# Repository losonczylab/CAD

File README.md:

# Hardware
Includes AutoDesk Inventor projects used for lab rigs, other miscellaneous CAD files, Adobe Illustrator files used for laser cutting, and user guides for constructing assemblies.

## Useful Programs
  - <a href="https://www.arduino.cc/en/software">Arduino IDE</a> - used to flash the Behavior Controller and Position Controller programs onto the Arduino Due and Arduino Nanos respectively.
  - <a href="https://www.kicad.org/">KiCad</a>
  - <a href ="https://www.autodesk.com/products/inventor">AutoDesk Inventor 2024 or Later (academic licenses available)</a>

## Electronics
  - Arduino program for Behavior Controller and Position Controller
  - KiCad files for PCB boards for the Behavior and Position Controllers
  - PDF manual for assembling a complete electronics box

## Full-Size-Rig
  - CAD files for frames holding full size displays

## Illustrator Files
- Adobe Illustrator files for custom made parts from laser-cut arylic

## Implant
- CAD files for metal implant used to head-fix mice.

## Implant Holder
- CAD files for implant holder.

## Tablet Rig
  - CAD files for frames holding tablet displays

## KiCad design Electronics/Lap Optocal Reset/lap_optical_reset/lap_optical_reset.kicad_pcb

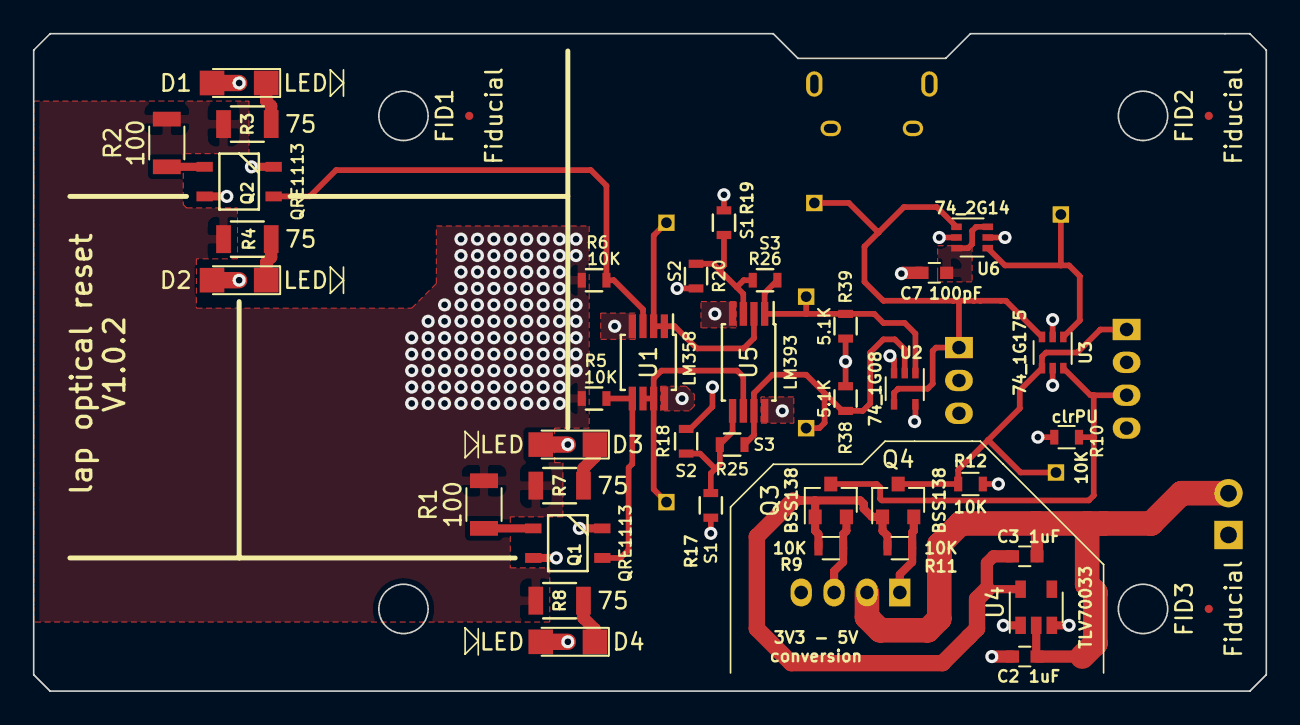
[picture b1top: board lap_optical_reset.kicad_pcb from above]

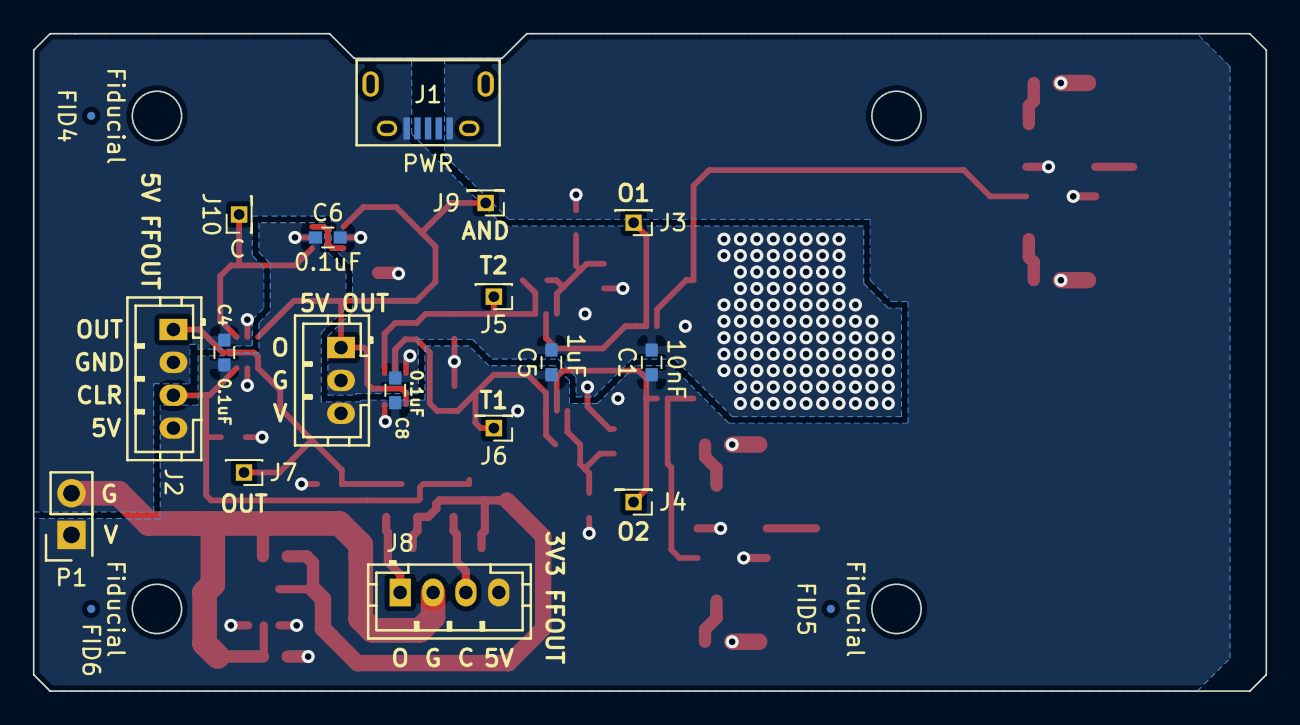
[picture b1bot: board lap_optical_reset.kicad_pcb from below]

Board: 2 copper layers, 75.0 x 40.0 mm, 60 parts (20 on the bottom side), 24 nets.

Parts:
C1: 10nF; C_0603
C2, C3, C5: 1uF; C_0603
C4, C6, C8: 0.1uF; C_0603
C7: 100pF; C_0603
D1, D2, D3, D4: LED; LED_1206
FID1, FID2, FID3, FID4, FID5, FID6: Fiducial; Fiducial_0.5mm_Dia_1mm_Outer
J1: PWR; USB_Micro-B
J2: 5V FFOUT; Connectors_JST_B4B-PH-K
J3: O1; Pin_Header_Straight_1x01_Pitch1.27mm
J4: O2; Pin_Header_Straight_1x01_Pitch1.27mm
J5: T2; Pin_Header_Straight_1x01_Pitch1.27mm
J6: T1; Pin_Header_Straight_1x01_Pitch1.27mm
J7: FFO; Pin_Header_Straight_1x01_Pitch1.27mm
J8: 3V3 FFOUT; Connectors_JST_B4B-PH-K
J9: AO; Pin_Header_Straight_1x01_Pitch1.27mm
J10: C; Pin_Header_Straight_1x01_Pitch1.27mm
J11: 5V OUT; Connectors_JST_B3B-PH-K
P1: TESTPWR; Pin_Header_Straight_2x01
Q1, Q2: QRE1113
Q3, Q4: BSS138; SOT-23
R1, R2: 100; R_1206
R3, R4, R7, R8: 75; R_1206
R5, R6, R9, R10, R11, R12: 10K; R_0603
R17, R19: S1; R_0603
R18, R20: S2; R_0603
R25, R26: S3; R_0603
R38, R39: 5.1K; R_0603
U1: LM358; MSOP-8_3x3mm_Pitch0.65mm
U2: 74_1G08; SOT-353_SC-70-5
U3: 74_1G175; SOT-363_SC-70-6
U4: TLV70033; SOT-23-5
U5: LM393; TSSOP-8_4.4x3mm_Pitch0.65mm
U6: 74_2G14; SOT-363_SC-70-6

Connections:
GND: C1.2, C2.2, C3.2, C4.2, C5.2, C6.2, C7.2, C8.2, J1.5, J2.2, J8.2, J11.2, P1.2, R1.2, R2.2, R3.1, R4.1, R5.2, R6.2, R7.1, R8.1, R18.2, R20.2, U1.4, U2.3, U3.2, U4.2, U5.4, U6.2
unnamed: C7.1, U6.3, U6.6
unnamed: D1.1, R3.2
unnamed: D2.1, R4.2
unnamed: D3.1, R7.2
unnamed: D4.1, R8.2
unnamed: J2.1, J7.1, Q4.3, R12.1, U3.4
unnamed: J2.3, Q3.3, R10.1, U3.6
unnamed: J3.1, U1.1, U1.2, U5.2
unnamed: J4.1, U1.6, U1.7, U5.6
unnamed: J5.1, R26.2, R39.1, U2.1, U5.1
unnamed: J6.1, R25.2, R38.1, U2.2, U5.7
unnamed: J8.1, Q4.2, R11.2
unnamed: J8.3, Q3.2, R9.2
unnamed: J10.1, U3.1, U6.4
unnamed: J9.1, J11.1, U2.4, U3.3, U6.1
unnamed: Q1.2, R1.1
unnamed: Q1.4, R5.1, U1.5
unnamed: Q2.2, R2.1
unnamed: Q2.4, R6.1, U1.3
unnamed: R17.2, R18.1, R25.1, U5.5
unnamed: R19.2, R20.1, R26.1, U5.3
VCC: C1.1, C2.1, C4.1, C5.1, C6.1, C8.1, D1.2, D2.2, D3.2, D4.2, J1.1, J2.4, J8.4, J11.3, P1.1, Q1.1, Q1.3, Q2.1, Q2.3, R10.2, R12.2, R17.1, R19.1, R38.2, R39.2, U1.8, U2.5, U3.5, U4.1, U4.3, U5.8, U6.5
VDD: C3.1, Q3.1, Q4.1, R9.1, R11.1, U4.5

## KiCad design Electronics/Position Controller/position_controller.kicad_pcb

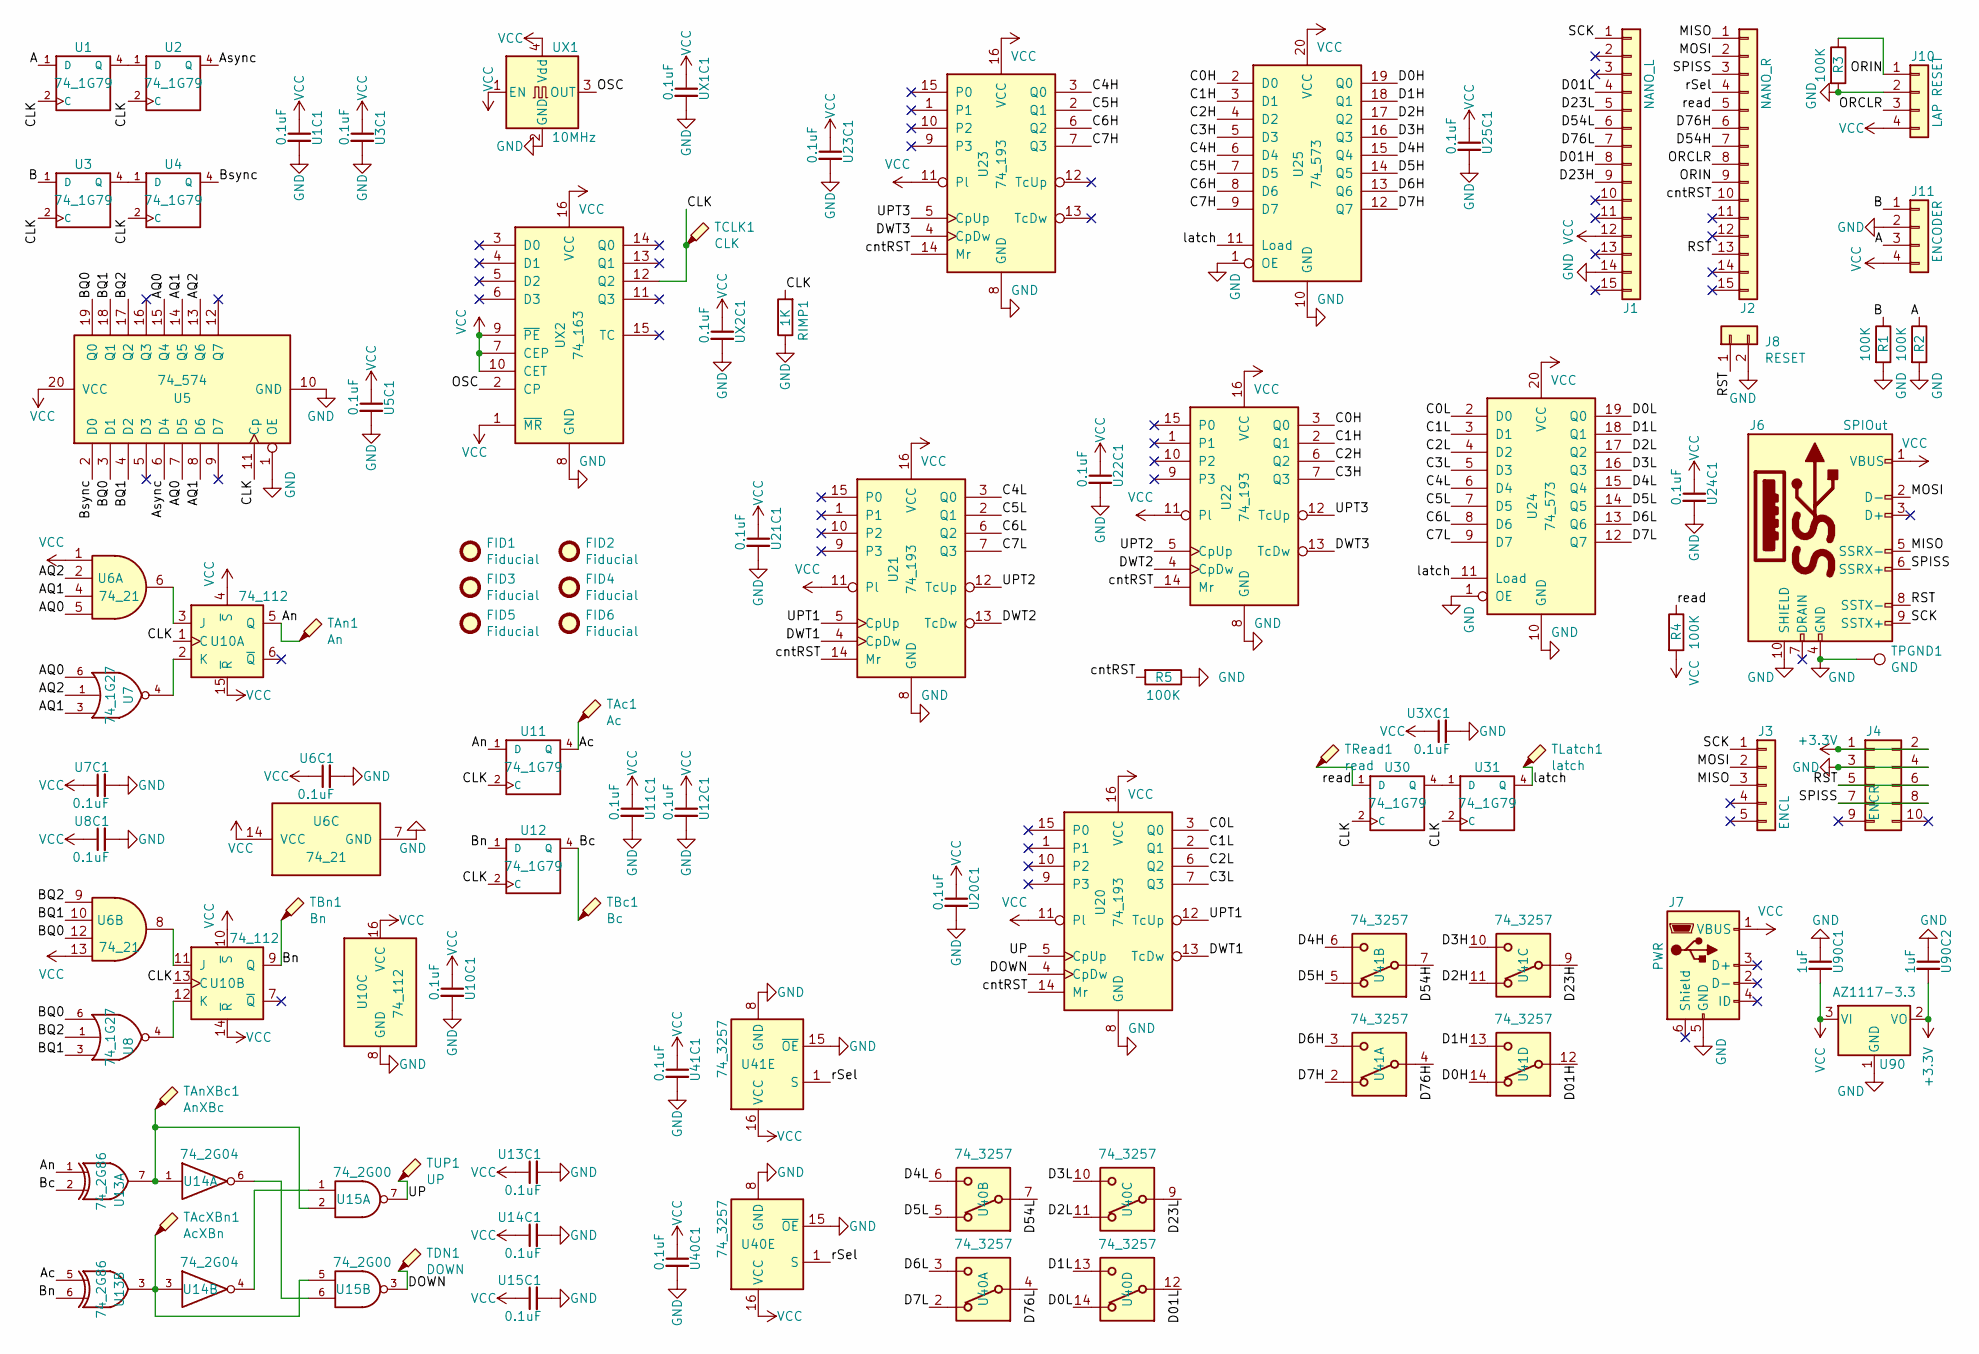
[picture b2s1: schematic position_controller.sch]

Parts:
FID1, FID2, FID3, FID4, FID5, FID6: Fiducial; Fiducial_0.5mm_Dia_1mm_Outer
J1: NANO_L; Pin_Header_Straight_1x15_Pitch2.54mm
J2: NANO_R; Pin_Header_Straight_1x15_Pitch2.54mm
J3: ENCL; Pin_Header_Straight_1x05_Pitch2.54mm
J4: ENCR; Pin_Header_Straight_2x05_Pitch2.54mm
J6: SPIOut; USB3_A_vertical_molex; Manufacturer Part Number 0484080003; digikey WM10421-ND
J7: PWR; USB_Micro-B; Manufacturer Part Number 10118194-0001LF; digikey 609-4618-1-ND
J8: RESET; Connectors_JST_B2B-PH-K; Manufacturer Part Number B2B-PH-K-S, S2B-PH-K-S; digikey 455-1704-ND
J10: LAP RESET; Connectors_JST_B4B-PH-K; Manufacturer Part Number B4B-PH-K-S, S4B-PH-K-S; digikey 455-1706-ND
J11: ENCODER; Connectors_JST_B4B-PH-K; Manufacturer Part Number B4B-PH-K-S, S4B-PH-K-S; digikey 455-1706-ND
R1, R2, R3, R4, R5: 100K; R_0603
RIMP1: 1K; R_0603
TAc1: Ac; Measurement_Point_Round-SMD-Pad_Small
TAcXBn1: AcXBn; Measurement_Point_Round-SMD-Pad_Small
TAn1: An; Measurement_Point_Round-SMD-Pad_Small
TAnXBc1: AnXBc; Measurement_Point_Round-SMD-Pad_Small
TBc1: Bc; Measurement_Point_Round-SMD-Pad_Small
TBn1: Bn; Measurement_Point_Round-SMD-Pad_Small
TCLK1: CLK; Measurement_Point_Round-SMD-Pad_Small
TDN1: DOWN; Measurement_Point_Round-SMD-Pad_Small
TLatch1: latch; Measurement_Point_Round-SMD-Pad_Small
TPGND1: GND; Measurement_Point_Round-TH_Big
TRead1: read; Measurement_Point_Round-SMD-Pad_Small
TUP1: UP; Measurement_Point_Round-SMD-Pad_Small
U1, U2, U3, U4, U11, U12, U30, U31: 74_1G79; SOT-23-5; Manufacturer Part Number 74LVC1G79GV,125; digikey 1727-6079-1-ND
U1C1, U3C1, U3XC1, U5C1, U6C1, U7C1, U8C1, U10C1, U11C1, U12C1, U13C1, U14C1, U15C1, U20C1, U21C1, U22C1, U23C1, U24C1, U25C1, U40C1, U41C1: 0.1uF; C_0603
U5: 74_574; TSSOP-20_4.4x6.5mm_Pitch0.65mm; Manufacturer Part Number SN74LV574APWR; digikey 296-12285-1-ND
U6: 74_21; TSSOP-14_4.4x5mm_Pitch0.65mm; Manufacturer Part Number SN74LV21APWRG4; digikey SN74LV21APWRG4-ND
U7, U8: 74_1G27; SOT-363_SC-70-6; Manufacturer Part Number SN74LVC1G27DCKR; digikey 296-18764-1-ND
U10: 74_112; TSSOP-16_4.4x5mm_Pitch0.65mm; Manufacturer Part Number 74VHC112MTCX; digikey 74VHC112MTCXCT-ND
U13: 74_2G86; MSOP-8_3x3mm_Pitch0.65mm; Manufacturer Part Number SN74LVC2G86DCTR; digikey 296-13274-1-ND
U14: 74_2G04; SOT-363_SC-70-6; Manufacturer Part Number SN74LVC2G04DCKRG4; digikey 296-51609-1-ND
U15: 74_2G00; MSOP-8_3x3mm_Pitch0.65mm; Manufacturer Part Number SN74LVC2G00DCTR; digikey 296-13257-1-ND
U20, U21, U22, U23: 74_193; TSSOP-16_4.4x5mm_Pitch0.65mm; Manufacturer Part Number 74HCT193PW-Q100J; digikey 1727-7974-1-ND
U24, U25: 74_573; TSSOP-20_4.4x6.5mm_Pitch0.65mm; Manufacturer Part Number SN74LV573APWR; digikey 296-3840-1-ND
U40, U41: 74_3257; TSSOP-16_4.4x5mm_Pitch0.65mm; Manufacturer Part Number 74FST3257DTR2G; digikey 74FST3257DTR2GOSCT-ND
U90: AZ1117-3.3; SOT-223-3_TabPin2; Manufacturer Part Number AZ1117IH-3.3TRG1; digikey AZ1117IH-3.3TRG1DICT-ND
U90C1, U90C2: 1uF; C_0603
UX1: 10MHz; Oscillator_SMD_EuroQuartz_XO53-4pin_5.0x3.2mm; Manufacturer Part Number ECS-3961-100-AU-TR; digikey XC1898CT-ND
UX1C1, UX2C1: 0.1uF; C_0603
UX2: 74_163; TSSOP-16_4.4x5mm_Pitch0.65mm; Manufacturer Part Number SN74LV163APWR; digikey 296-12347-1-ND

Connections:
+3V3: J4.1, J4.2, U90.2 (VO), U90C2.2
/A: J11.3, R2.1, U1.1 (D)
/AQ0: U5.7 (D5), U5.15 (Q4), U6.5, U7.6
/AQ1: U5.8 (D6), U5.14 (Q5), U6.4, U7.3
/AQ2: U5.13 (Q6), U6.2, U7.1
/Ac: TAc1.1, U11.4 (Q), U13.5
/An: TAn1.1, U10.5 (Q), U11.1 (D), U13.1
/Async: U2.4 (Q), U5.6 (D4)
/B: J11.1, R1.1, U3.1 (D)
/BQ0: U5.3 (D1), U5.19 (Q0), U6.12, U8.6
/BQ1: U5.4 (D2), U5.18 (Q1), U6.10, U8.3
/BQ2: U5.17 (Q2), U6.9, U8.1
/Bc: TBc1.1, U12.4 (Q), U13.2
/Bn: TBn1.1, U10.9 (Q), U12.1 (D), U13.6
/Bsync: U4.4 (Q), U5.2 (D0)
/C0H: U22.3 (Q0), U25.2 (D0)
/C0L: U20.3 (Q0), U24.2 (D0)
/C1H: U22.2 (Q1), U25.3 (D1)
/C1L: U20.2 (Q1), U24.3 (D1)
/C2H: U22.6 (Q2), U25.4 (D2)
/C2L: U20.6 (Q2), U24.4 (D2)
/C3H: U22.7 (Q3), U25.5 (D3)
/C3L: U20.7 (Q3), U24.5 (D3)
/C4H: U23.3 (Q0), U25.6 (D4)
/C4L: U21.3 (Q0), U24.6 (D4)
/C5H: U23.2 (Q1), U25.7 (D5)
/C5L: U21.2 (Q1), U24.7 (D5)
/C6H: U23.6 (Q2), U25.8 (D6)
/C6L: U21.6 (Q2), U24.8 (D6)
/C7H: U23.7 (Q3), U25.9 (D7)
/C7L: U21.7 (Q3), U24.9 (D7)
/CLK: RIMP1.2, TCLK1.1, U1.2 (C), U2.2 (C), U3.2 (C), U4.2 (C), U5.11 (Cp), U10.1 (C), U10.13 (C), U11.2 (C), U12.2 (C), U30.2 (C), U31.2 (C), UX2.12 (Q2)
/D0H: U25.19 (Q0), U41.14
/D0L: U24.19 (Q0), U40.14
/D01H: J1.8, U41.12
/D1H: U25.18 (Q1), U41.13
/D01L: J1.4, U40.12
/D1L: U24.18 (Q1), U40.13
/D2H: U25.17 (Q2), U41.11
/D2L: U24.17 (Q2), U40.11
/D3H: U25.16 (Q3), U41.10
/D3L: U24.16 (Q3), U40.10
/D4H: U25.15 (Q4), U41.6
/D4L: U24.15 (Q4), U40.6
/D5H: U25.14 (Q5), U41.5
/D5L: U24.14 (Q5), U40.5
/D6H: U25.13 (Q6), U41.3
/D6L: U24.13 (Q6), U40.3
/D7H: U25.12 (Q7), U41.2
/D7L: U24.12 (Q7), U40.2
/D23H: J1.9, U41.9
/D23L: J1.5, U40.9
/D54H: J2.7, U41.7
/D54L: J1.6, U40.7
/D76H: J2.6, U41.4
/D76L: J1.7, U40.4
/DOWN: TDN1.1, U15.3, U20.4 (CpDw)
/DWT1: U20.13 (TcDw), U21.4 (CpDw)
/DWT2: U21.13 (TcDw), U22.4 (CpDw)
/DWT3: U22.13 (TcDw), U23.4 (CpDw)
/MISO: J2.1, J3.3, J6.5 (SSRX-)
/MOSI: J2.2, J3.2, J6.2 (D-)
/ORCLR: J2.8, J10.3
/ORIN: J2.9, J10.1, R3.1
/OSC: UX1.3 (OUT), UX2.2 (CP)
/RST: J2.13, J4.5, J4.6, J6.8 (SSTX-), J8.1
/SCK: J1.1, J3.1, J6.9 (SSTX+)
/SPISS: J2.3, J4.7, J4.8, J6.6 (SSRX+)
/UP: TUP1.1, U15.7, U20.5 (CpUp)
/UPT1: U20.12 (TcUp), U21.5 (CpUp)
/UPT2: U21.12 (TcUp), U22.5 (CpUp)
/UPT3: U22.12 (TcUp), U23.5 (CpUp)
/cntRST: J2.10, R5.2, U20.14 (Mr), U21.14 (Mr), U22.14 (Mr), U23.14 (Mr)
/latch: TLatch1.1, U24.11 (Load), U25.11 (Load), U31.4 (Q)
/rSel: J2.4, U40.1 (S), U41.1 (S)
/read: J2.5, R4.1, TRead1.1, U30.1 (D)
GND: J1.14, J4.3, J4.4, J6.4 (GND), J6.10 (SHIELD), J7.5 (GND), J8.2, J10.2, J11.2, R1.2, R2.2, R3.2, R5.1, RIMP1.1, TPGND1.1, U1.3 (GND), U1C1.2, U2.3 (GND), U3.3 (GND), U3C1.2, U3XC1.2, U4.3 (GND), U5.1 (OE), U5.10 (GND), U5C1.2, U6.7 (GND), U6C1.2, U7.2 (GND), U7C1.2, U8.2 (GND), U8C1.2, U10.8 (GND), U10C1.2, U11.3 (GND), U11C1.2, U12.3 (GND), U12C1.2, U13.4 (GND), U13C1.2, U14.2 (GND), U14C1.2, U15.4 (GND), U15C1.2, U20.8 (GND), U20C1.2, U21.8 (GND), U21C1.2, U22.8 (GND), U22C1.2, U23.8 (GND), U23C1.2, U24.1 (OE), U24.10 (GND), U24C1.2, U25.1 (OE), U25.10 (GND), U25C1.2, U30.3 (GND), U31.3 (GND), U40.8 (GND), U40.15 (~OE), U40C1.2, U41.8 (GND), U41.15 (~OE), U41C1.2, U90.1 (GND), U90C1.1, U90C2.1, UX1.2 (GND), UX1C1.2, UX2.8 (GND), UX2C1.2
unnamed: TAcXBn1.1, U13.3, U14.3, U15.5
unnamed: TAnXBc1.1, U13.7, U14.1, U15.2
unnamed: U1.4 (Q), U2.1 (D)
unnamed: U3.4 (Q), U4.1 (D)
unnamed: U7.4, U10.2 (K)
unnamed: U6.6, U10.3 (J)
unnamed: U6.8, U10.11 (J)
unnamed: U8.4, U10.12 (K)
unnamed: U14.4, U15.1
unnamed: U14.6, U15.6
unnamed: U30.4 (Q), U31.1 (D)
VCC: J1.12, J6.1 (VBUS), J7.1 (VBUS), J10.4, J11.4, R4.2, U1.5 (VCC), U1C1.1, U2.5 (VCC), U3.5 (VCC), U3C1.1, U3XC1.1, U4.5 (VCC), U5.20 (VCC), U5C1.1, U6.1, U6.13, U6.14 (VCC), U6C1.1, U7.5 (VCC), U7C1.1, U8.5 (VCC), U8C1.1, U10.4 (~S), U10.10 (~S), U10.14 (~R), U10.15 (~R), U10.16 (VCC), U10C1.1, U11.5 (VCC), U11C1.1, U12.5 (VCC), U12C1.1, U13.8 (VCC), U13C1.1, U14.5 (VCC), U14C1.1, U15.8 (VCC), U15C1.1, U20.11 (Pl), U20.16 (VCC), U20C1.1, U21.11 (Pl), U21.16 (VCC), U21C1.1, U22.11 (Pl), U22.16 (VCC), U22C1.1, U23.11 (Pl), U23.16 (VCC), U23C1.1, U24.20 (VCC), U24C1.1, U25.20 (VCC), U25C1.1, U30.5 (VCC), U31.5 (VCC), U40.16 (VCC), U40C1.1, U41.16 (VCC), U41C1.1, U90.3 (VI), U90C1.2, UX1.1 (EN), UX1.4 (Vdd), UX1C1.1, UX2.1 (~MR), UX2.7 (CEP), UX2.9 (~PE), UX2.10 (CET), UX2.16 (VCC), UX2C1.1

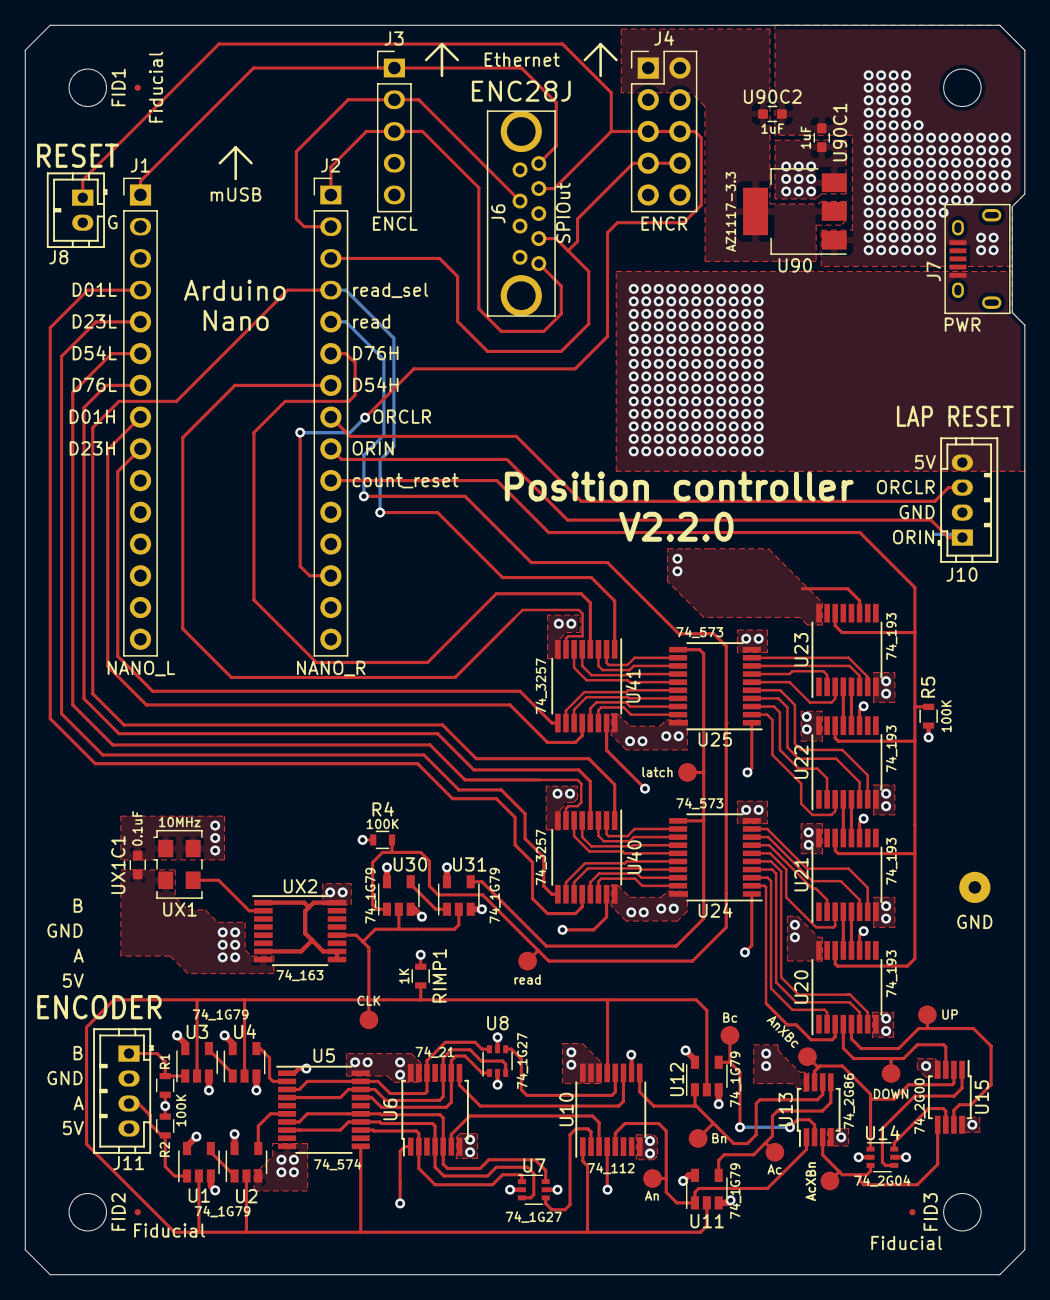
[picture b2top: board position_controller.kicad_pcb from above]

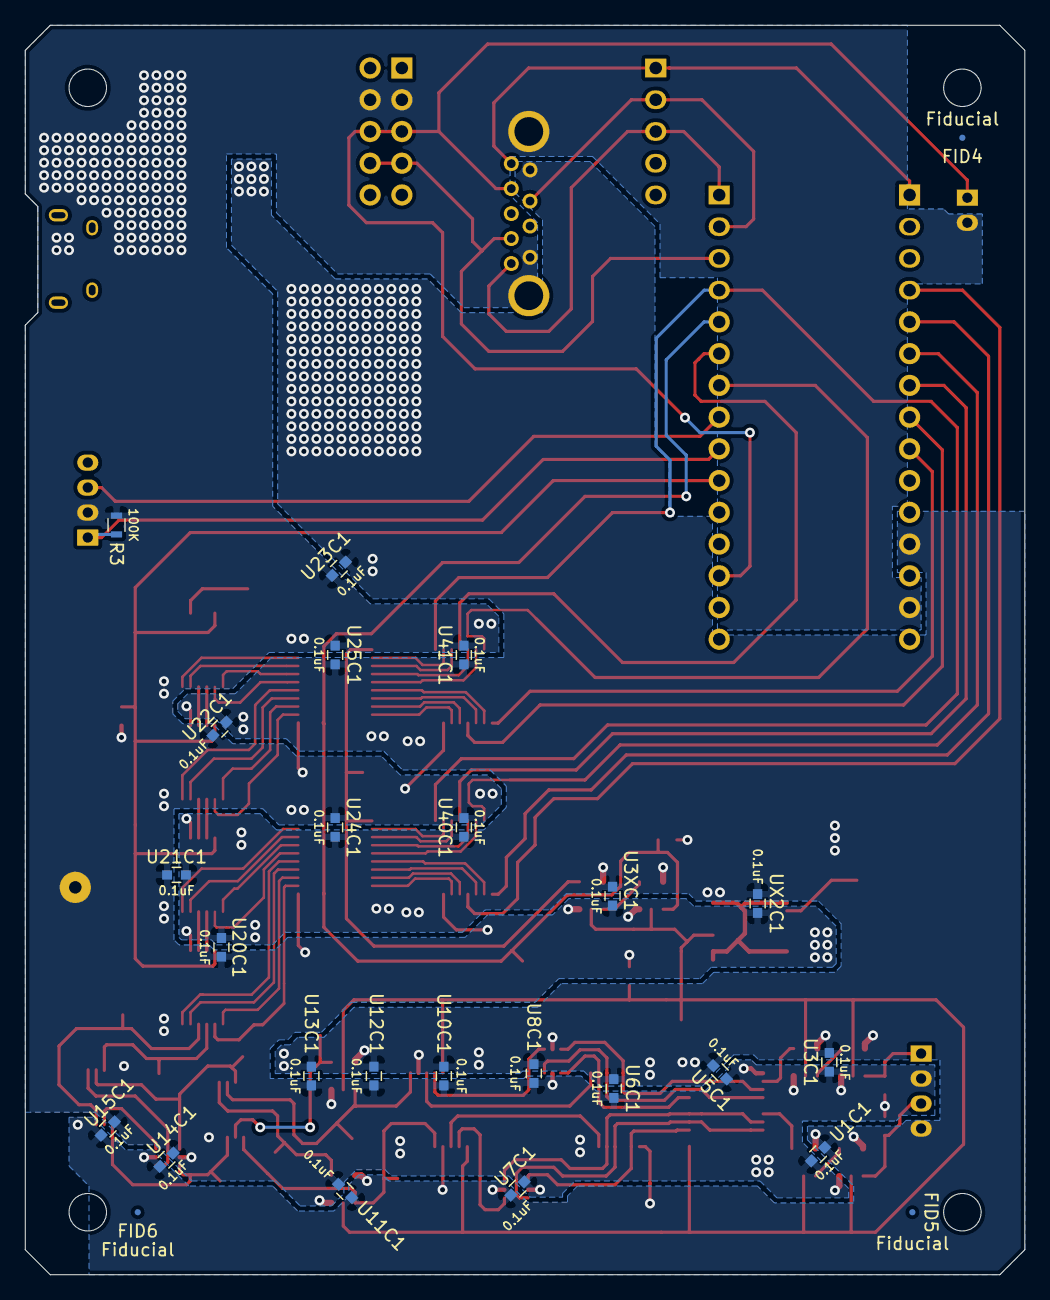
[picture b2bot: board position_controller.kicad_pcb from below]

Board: 2 copper layers, 80.0 x 100.0 mm, 85 parts (26 on the bottom side), 89 nets.

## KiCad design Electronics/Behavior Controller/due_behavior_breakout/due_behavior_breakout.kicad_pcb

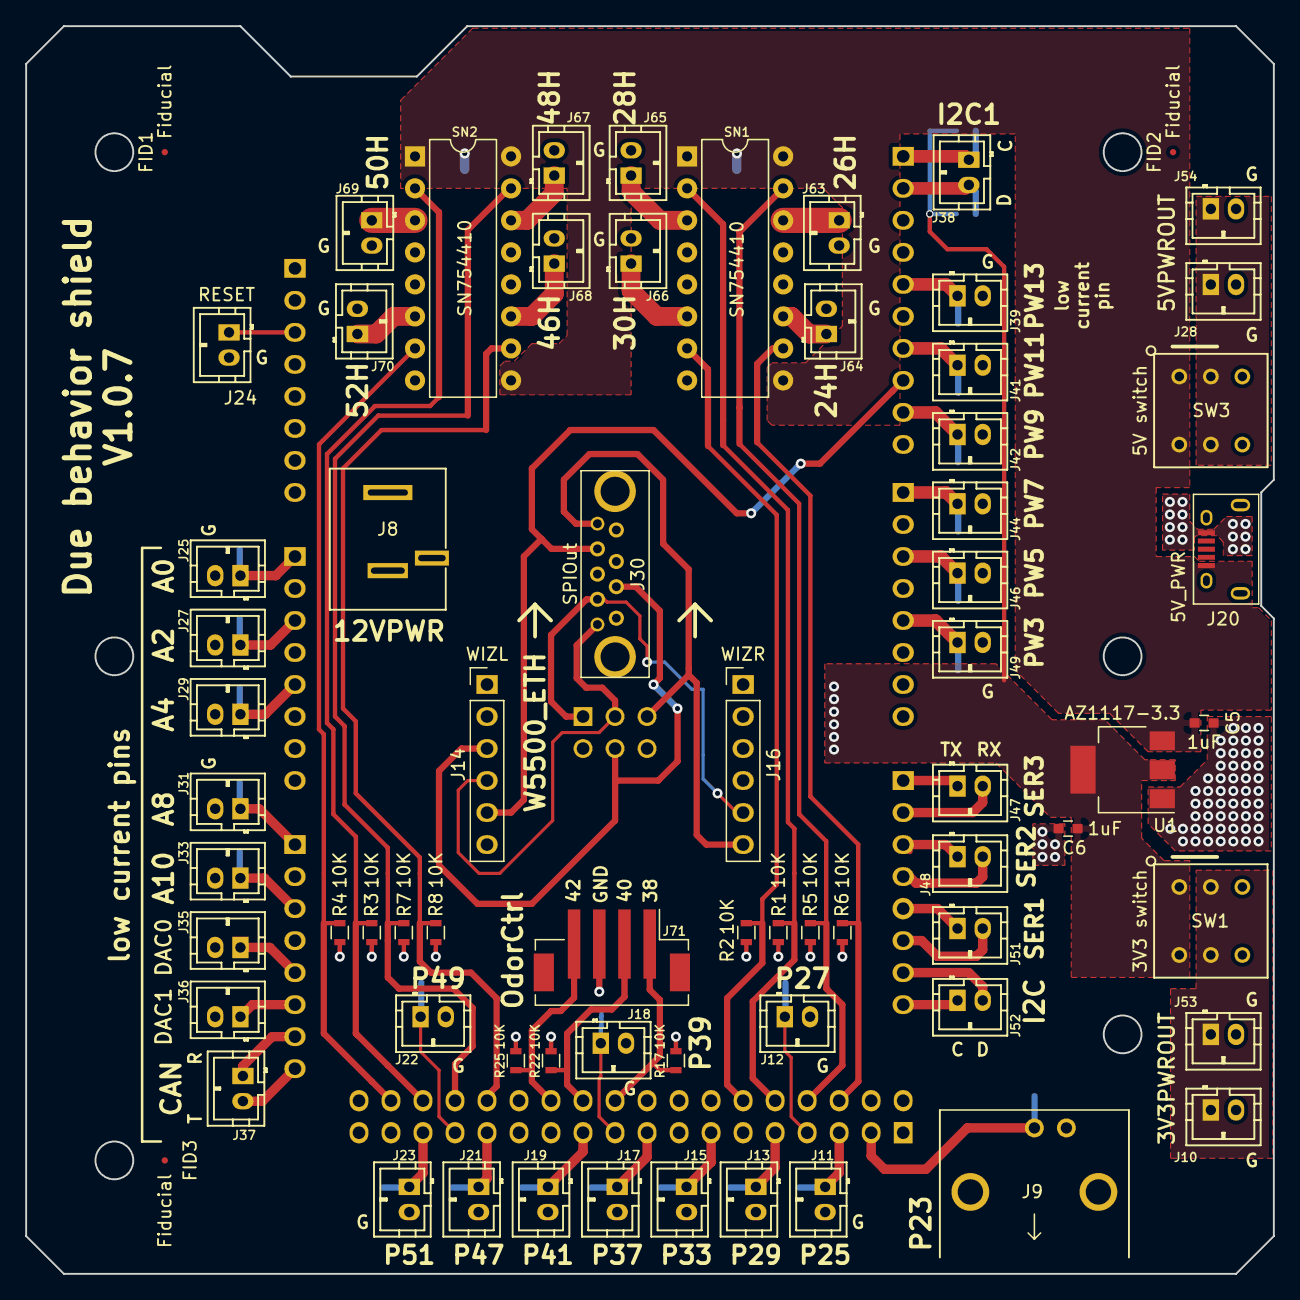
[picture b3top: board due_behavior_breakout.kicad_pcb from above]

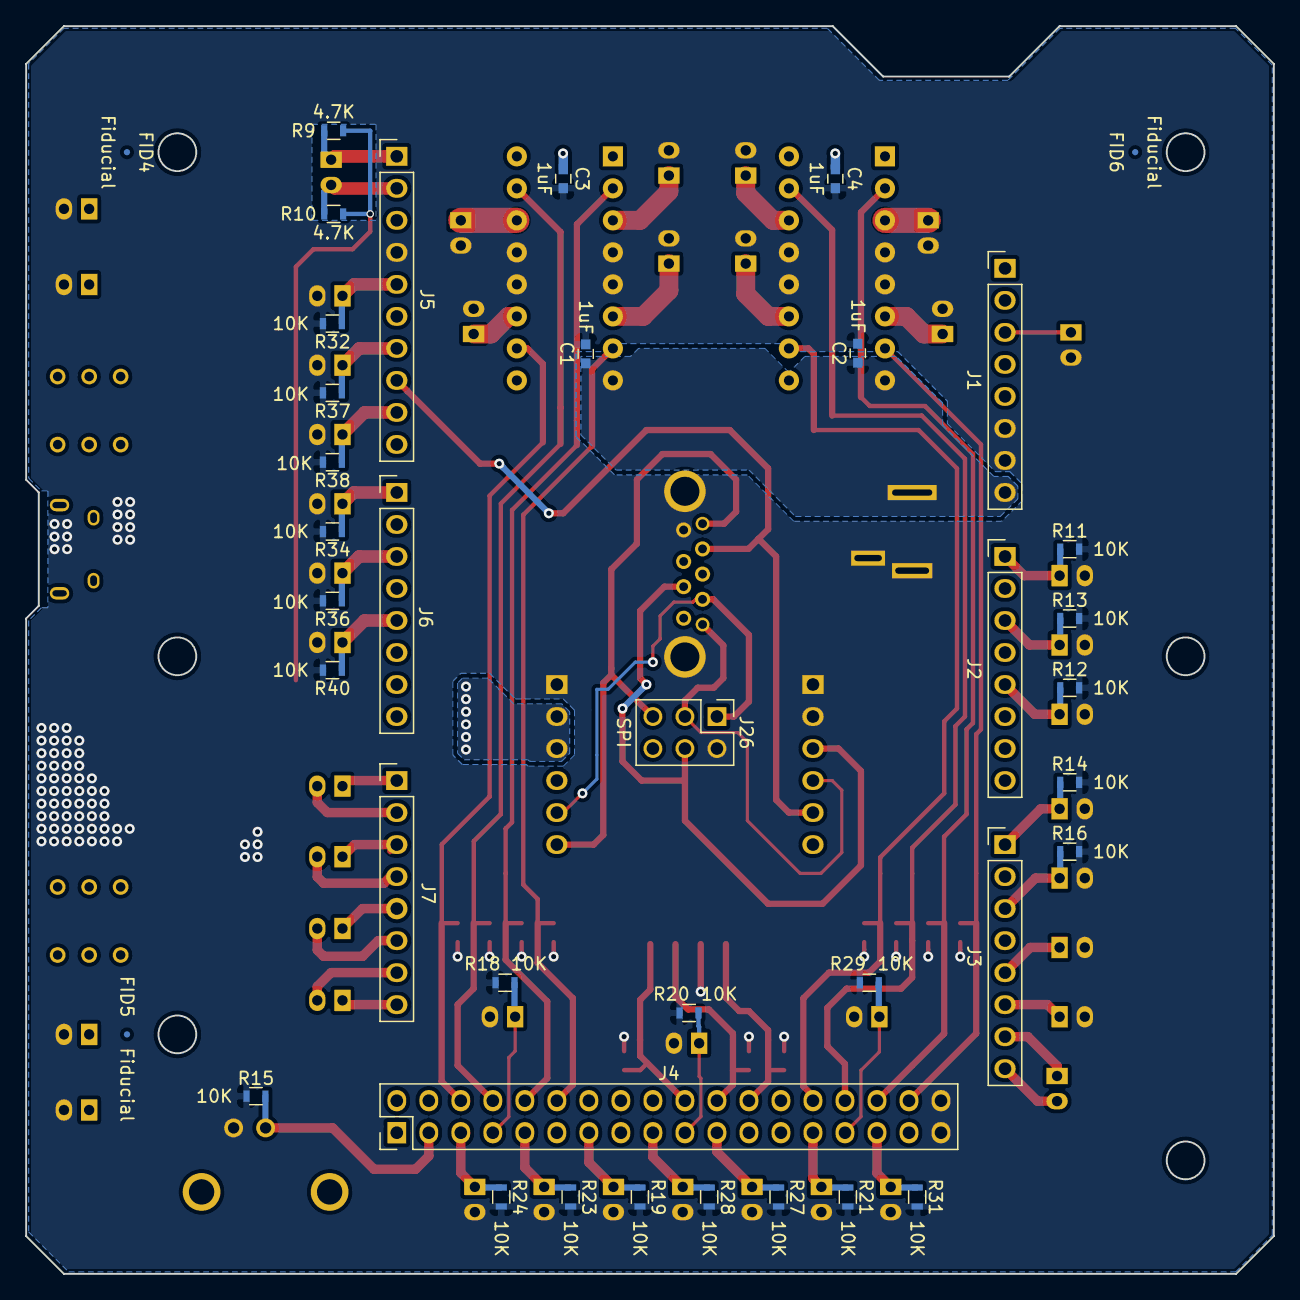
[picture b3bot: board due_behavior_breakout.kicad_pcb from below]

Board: 2 copper layers, 99.0 x 99.0 mm, 109 parts (39 on the bottom side), 67 nets.

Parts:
C1, C2, C3, C4, C5, C6: 1uF; C_0603
FID1, FID2, FID3, FID4, FID5, FID6: Fiducial; Fiducial_0.5mm_Dia_1mm_Outer
J1: UpperLeft; Pin_Header_Straight_1x08_Pitch2.54mm
J2: MiddleLeft; Pin_Header_Straight_1x08_Pitch2.54mm
J3: LowerLeft; Pin_Header_Straight_1x08_Pitch2.54mm
J4: Bottom; Pin_Header_Straight_2x18_Pitch2.54mm
J5: UpperRight; Pin_Header_Straight_1x10_Pitch2.54mm
J6: MiddleRight; Pin_Header_Straight_1x08_Pitch2.54mm
J7: LowerRight; Pin_Header_Straight_1x08_Pitch2.54mm
J8: 12VPWR; barrel_jack_2.1X5.5mm
J9: P23; BNC_right_angle
J10, J53: 3V3PWROUT; Connectors_JST_B2B-PH-K
J11: P25; Connectors_JST_B2B-PH-K
J12: P27; Connectors_JST_B2B-PH-K
J13: P29; Connectors_JST_B2B-PH-K
J14: WIZL; Pin_Header_Straight_1x06_Pitch2.54mm
J15: P33; Connectors_JST_B2B-PH-K
J16: WIZR; Pin_Header_Straight_1x06_Pitch2.54mm
J17: P37; Connectors_JST_B2B-PH-K
J18: P39; Connectors_JST_B2B-PH-K
J19: P41; Connectors_JST_B2B-PH-K
J20: 5V_PWR; USB_Micro-B
J21: P47; Connectors_JST_B2B-PH-K
J22: P49; Connectors_JST_B2B-PH-K
J23: P51; Connectors_JST_B2B-PH-K
J24: RESET; Connectors_JST_B2B-PH-K
J25: A0; Connectors_JST_B2B-PH-K
J26: SPI; Pin_Header_Straight_2x03_Pitch2.54mm
J27: A2; Connectors_JST_B2B-PH-K
J28, J54: 5VPWROUT; Connectors_JST_B2B-PH-K
J29: A4; Connectors_JST_B2B-PH-K
J30: SPIOut; USB3_A_vertical_molex
J31: A8; Connectors_JST_B2B-PH-K
J33: A10; Connectors_JST_B2B-PH-K
J35: DAC0; Connectors_JST_B2B-PH-K
J36: DAC1; Connectors_JST_B2B-PH-K
J37: CAN; Connectors_JST_B2B-PH-K
J38: I2C1; Connectors_JST_B2B-PH-K
J39: PW13; Connectors_JST_B2B-PH-K
J41: PW11; Connectors_JST_B2B-PH-K
J42: PW9; Connectors_JST_B2B-PH-K
J44: PW7; Connectors_JST_B2B-PH-K
J46: PW5; Connectors_JST_B2B-PH-K
J47: SER3; Connectors_JST_B2B-PH-K
J48: SER2; Connectors_JST_B2B-PH-K
J49: PW3; Connectors_JST_B2B-PH-K
J51: SER1; Connectors_JST_B2B-PH-K
J52: I2C; Connectors_JST_B2B-PH-K
J63: 26H; Connectors_JST_B2B-PH-K
J64: 24H; Connectors_JST_B2B-PH-K
J65: 28H; Connectors_JST_B2B-PH-K
J66: 30H; Connectors_JST_B2B-PH-K
J67: 48H; Connectors_JST_B2B-PH-K
J68: 46H; Connectors_JST_B2B-PH-K
J69: 50H; Connectors_JST_B2B-PH-K
J70: 52H; Connectors_JST_B2B-PH-K
J71: OdorCtrl; JST_PH_B4B-PH-SM4-TB_04x2.00mm_Straight
R1, R2, R3, R4, R5, R6, R7, R8, R11, R12, R13, R14, R15, R16, R17, R18, R19, R20, R21, R22, R23, R24, R25, R27, R28, R29, R31, R32, R34, R36, R37, R38, R40: 10K; R_0603
R9, R10: 4.7K; R_0603
SN1, SN2: SN754410; DIP-16_W7.62mm
SW1: 3V3 switch; DPDT_Button_switch
SW3: 5V switch; DPDT_Button_switch
U1: AZ1117-3.3; SOT-223-3_TabPin2

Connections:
+3V3: C6.2, J16.2, J16.3, R9.1, R10.2, SW1.1, SW1.4, U1.2
+5V: C3.1, C4.1, C5.2, J20.1, SN1.1, SN1.9, SN1.16, SN2.1, SN2.9, SN2.16, SW3.1, SW3.4, U1.3
+12V: C1.1, C2.1, J1.8, J8.1, SN1.8, SN2.8
/23: J4.3, J9.1, R15.1
/24: J4.6, R6.1, SN1.10
/25: J4.5, J11.1, R24.1
/26: J4.8, R5.1, SN1.15
/27: J4.7, J12.1, R18.1
/28: J4.10, R1.2, SN1.2
/29: J4.9, J13.1, R23.1
/30: J4.12, R2.2, SN1.7
/33: J4.13, J15.1, R19.1
/37: J4.17, J17.1, R28.1
/38: J4.20, J71.1, R17.1
/39: J4.19, J18.1, R20.1
/40: J4.22, J71.2, R22.1
/41: J4.21, J19.1, R27.1
/42: J4.24, J71.4, R25.1
/46: J4.28, R8.1, SN2.10
/47: J4.27, J21.1, R21.1
/48: J4.30, R7.1, SN2.15
/49: J4.29, J22.1, R29.1
/50: J4.32, R3.2, SN2.2
/51: J4.31, J23.1, R31.1
/52: J4.34, R4.2, SN2.7
/A0: J2.1, J25.1, R11.1
/A2: J2.3, J27.1, R13.1
/A4: J2.5, J29.1, R12.1
/A8: J3.1, J31.1, R14.1
/A10: J3.3, J33.1, R16.1
/CANRX: J3.7, J37.1
/CANTX: J3.8, J37.2
/DAC0: J3.5, J35.1
/DAC1: J3.6, J36.1
/MISO: J16.6, J26.5, J30.5
/MOSI: J14.3, J26.4, J30.2
/PWM3: J6.5, J49.1, R40.1
/PWM5: J6.3, J46.1, R36.1
/PWM7: J6.1, J44.1, R34.1
/PWM9: J5.9, J42.1, R38.1
/PWM11: J5.7, J41.1, R37.1
/PWM13: J5.5, J39.1, R32.1
/RST: J16.5, J26.1, J30.8
/RX1: J7.6, J51.2
/RX2: J7.4, J48.2
/RX3: J7.2, J47.2
/Reset: J1.3, J24.1
/SCK: J14.4, J26.3, J30.9
/SCL: J7.8, J52.1
/SCL1: J5.1, J38.1, R9.2
/SDA: J7.7, J52.2
/SDA1: J5.2, J38.2, R10.1
/SPI_SS: J5.8, J14.5, J30.6
/TX1: J7.5, J51.1
/TX2: J7.3, J48.1
/TX3: J7.1, J47.1
GND: C1.2, C2.2, C3.2, C4.2, C5.1, C6.1, J1.6, J1.7, J4.35, J4.36, J5.4, J8.2, J8.3, J9.2, J10.2, J11.2, J12.2, J13.2, J14.1, J14.2, J15.2, J16.1, J17.2, J18.2, J19.2, J20.5, J21.2, J22.2, J23.2, J24.2, J25.2, J26.2, J27.2, J28.2, J29.2, J30.4, J30.10, J31.2, J33.2, J35.2, J36.2, J39.2, J41.2, J42.2, J44.2, J46.2, J49.2, J53.2, J54.2, J63.2, J64.2, J65.2, J66.2, J67.2, J68.2, J69.2, J70.2, J71.3, R1.1, R2.1, R3.1, R4.1, R5.2, R6.2, R7.2, R8.2, R11.2, R12.2, R13.2, R14.2, R15.2, R16.2, R17.2, R18.2, R19.2, R20.2, R21.2, R22.2, R23.2, R24.2, R25.2, R27.2, R28.2, R29.2, R31.2, R32.2, R34.2, R36.2, R37.2, R38.2, R40.2, SN1.4, SN1.5, SN1.12, SN1.13, SN2.4, SN2.5, SN2.12, SN2.13, U1.1
unnamed: J10.1, J53.1, SW1.2, SW1.5
unnamed: J28.1, J54.1, SW3.2, SW3.5
unnamed: J63.1, SN1.14
unnamed: J64.1, SN1.11
unnamed: J65.1, SN1.3
unnamed: J66.1, SN1.6
unnamed: J67.1, SN2.14
unnamed: J68.1, SN2.11
unnamed: J69.1, SN2.3
unnamed: J70.1, SN2.6

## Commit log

2023-11-21 added gitignore
2023-11-21 files for laser cutting
2023-11-21 first main commit
2024-03-18 electronics files
2024-03-20 remove optical lap reset from behavior controller folder
